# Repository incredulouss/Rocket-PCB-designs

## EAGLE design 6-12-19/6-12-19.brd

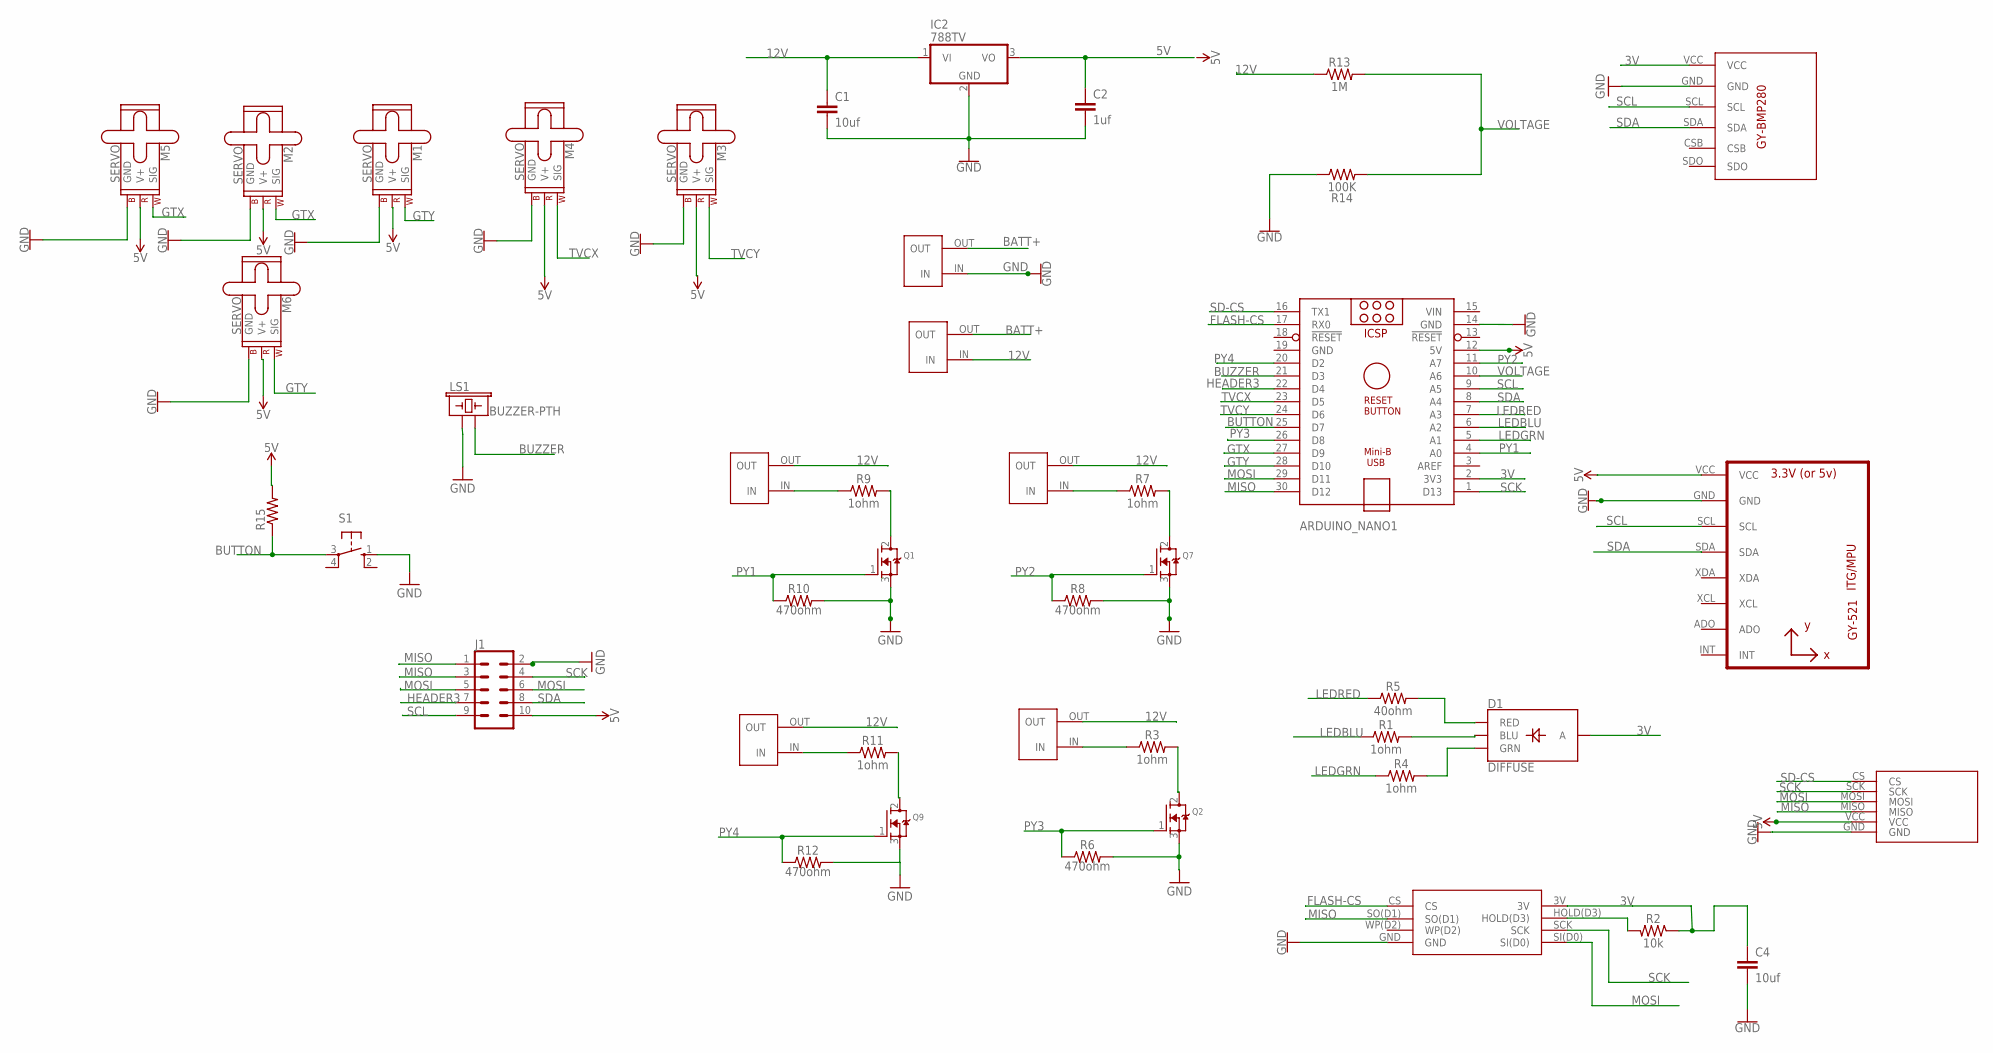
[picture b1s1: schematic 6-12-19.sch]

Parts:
ARDUINO_NANO1: ARDUINO_NANO
C1, C4: 10uf; CAP-PTH-2.54
C2: 1uf; CAP-PTH-2.54
D1: DIFFUSE; LED-RGB-THRU
IC2: 788TV; TO220V
J1: CONN_05X2NO_SILK; 2X5_NOSILK
LS1: BUZZER-PTH; BUZZER-12MM
M1, M2, M3, M4, M5, M6: SERVO; 1X03
Q1, Q2, Q7, Q9: MOSFET-NGDS_TO220V; TO220V
R1, R3, R4, R7, R9, R11: 1ohm; AXIAL-0.3
R2: 10k; AXIAL-0.3
R5: 40ohm; AXIAL-0.3
R6, R8, R10, R12: 470ohm; AXIAL-0.3
R13: 1M; AXIAL-0.3
R14: 100K; AXIAL-0.3
R15: FLIPFLOP-RES; 0805-THM
S1: 40-XX; B3F-40XX
U1: GY-521MPU6050; GY-521
U$1, U$6, U$7, U$11, U$13, U$31: TERMINALBLOCK
U$2: W25Q32FV
U$8: GY-BMP280
U$9: MICROSDCARD

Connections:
3V: ARDUINO_NANO1.2 (3V3), C4.1, D1.2 (A), R2.P$1 (1), U$2.3V, U$8.VCC
5V: ARDUINO_NANO1.12 (5V), C2.1, IC2.3 (VO), J1.10, M1.2 (V+), M2.2 (V+), M3.2 (V+), M4.2 (V+), M5.2 (V+), M6.2 (V+), R15.2, U1.VCC, U$9.VCC
12V: C1.1, IC2.1 (VI), R13.P$1 (1), U$1.IN, U$7.OUT, U$11.OUT, U$13.OUT, U$31.OUT
BATT+: U$1.OUT, U$6.OUT
BUTTON: ARDUINO_NANO1.25 (D7), R15.1, S1.3
BUZZER: ARDUINO_NANO1.21 (D3), LS1.- (2)
FLASH-CS: ARDUINO_NANO1.17 (RX0), U$2.CS
GND: ARDUINO_NANO1.14 (GND), ARDUINO_NANO1.19 (GND), C1.2, C2.2, C4.2, IC2.2 (GND), J1.2, LS1.+ (1), M1.3 (GND), M2.3 (GND), M3.3 (GND), M4.3 (GND), M5.3 (GND), M6.3 (GND), Q1.3 (S), Q2.3 (S), Q7.3 (S), Q9.3 (S), R6.P$2 (2), R8.P$2 (2), R10.P$2 (2), R12.P$2 (2), R14.P$1 (1), S1.1 (S), U1.GND, U$2.GND, U$6.IN, U$8.GND, U$9.GND
GTX: ARDUINO_NANO1.27 (D9), M2.1 (SIG), M5.1 (SIG)
GTY: ARDUINO_NANO1.28 (D10), M1.1 (SIG), M6.1 (SIG)
HEADER3: ARDUINO_NANO1.22 (D4), J1.7
LEDBLU: ARDUINO_NANO1.6 (A2), R1.P$1 (1)
LEDGRN: ARDUINO_NANO1.5 (A1), R4.P$1 (1)
LEDRED: ARDUINO_NANO1.7 (A3), R5.P$1 (1)
MISO: ARDUINO_NANO1.30 (D12), J1.1, J1.3, U$2.SO(D1), U$9.MISO
MOSI: ARDUINO_NANO1.29 (D11), J1.5, J1.6, U$2.SI(D0), U$9.MOSI
unnamed: R2.P$2 (2), U$2.HOLD(D3)
unnamed: R9.P$1 (1), U$31.IN
unnamed: Q1.2 (D), R9.P$2 (2)
unnamed: D1.1 (RED), R5.P$2 (2)
unnamed: D1.4 (BLU), R1.P$2 (2)
unnamed: D1.3 (GRN), R4.P$2 (2)
unnamed: R3.P$1 (1), U$7.IN
unnamed: Q2.2 (D), R3.P$2 (2)
unnamed: Q7.2 (D), R7.P$2 (2)
unnamed: R7.P$1 (1), U$11.IN
unnamed: R11.P$1 (1), U$13.IN
unnamed: Q9.2 (D), R11.P$2 (2)
PY1: ARDUINO_NANO1.4 (A0), Q1.1 (G), R10.P$1 (1)
PY2: ARDUINO_NANO1.11 (A7), Q7.1 (G), R8.P$1 (1)
PY3: ARDUINO_NANO1.26 (D8), Q2.1 (G), R6.P$1 (1)
PY4: ARDUINO_NANO1.20 (D2), Q9.1 (G), R12.P$1 (1)
SCK: ARDUINO_NANO1.1 (D13), J1.4, U$2.SCK, U$9.SCK
SCL: ARDUINO_NANO1.9 (A5), J1.9, U1.SCL, U$8.SCL
SD-CS: ARDUINO_NANO1.16 (TX1), U$9.CS
SDA: ARDUINO_NANO1.8 (A4), J1.8, U1.SDA, U$8.SDA
TVCX: ARDUINO_NANO1.23 (D5), M4.1 (SIG)
TVCY: ARDUINO_NANO1.24 (D6), M3.1 (SIG)
VIN: ARDUINO_NANO1.15 (VIN)
VOLTAGE: ARDUINO_NANO1.10 (A6), R13.P$2 (2), R14.P$2 (2)

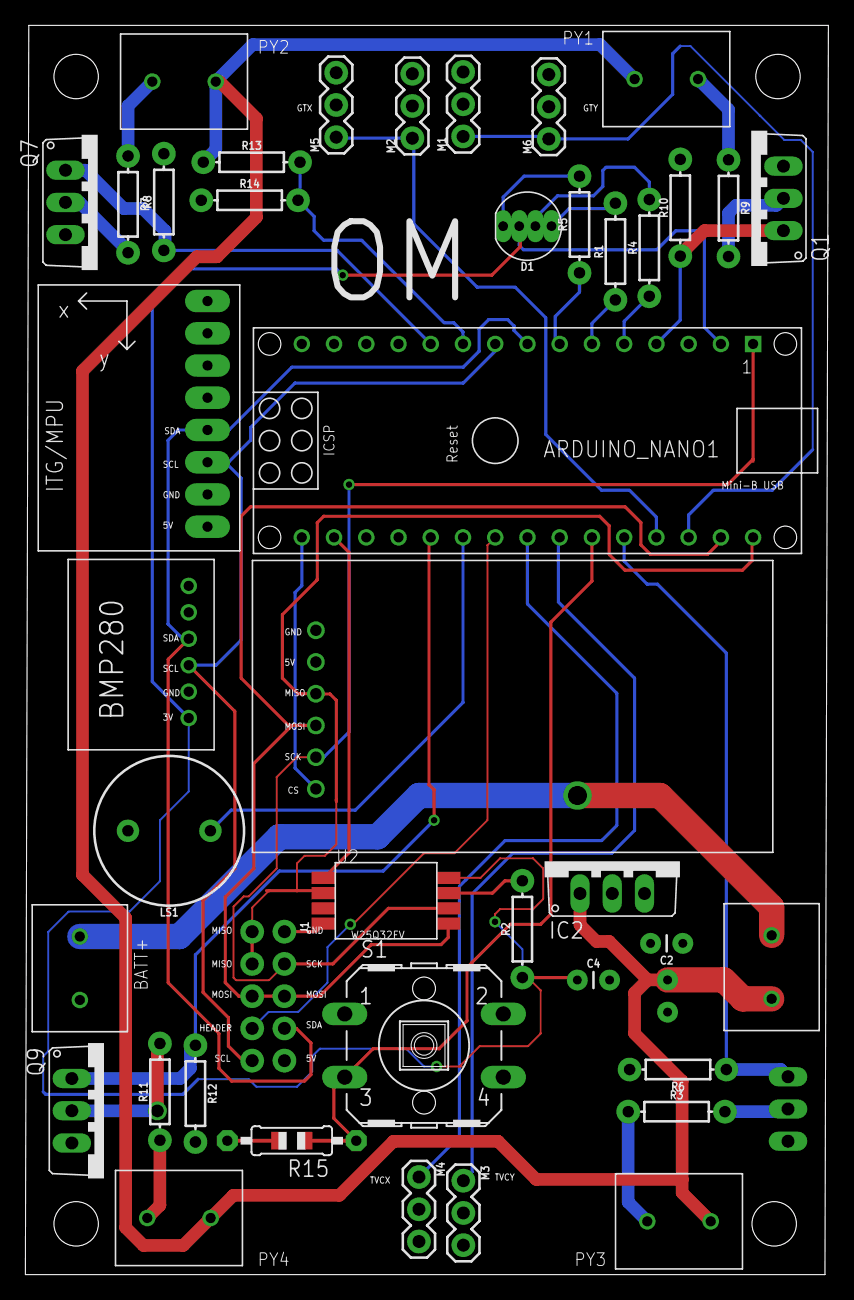
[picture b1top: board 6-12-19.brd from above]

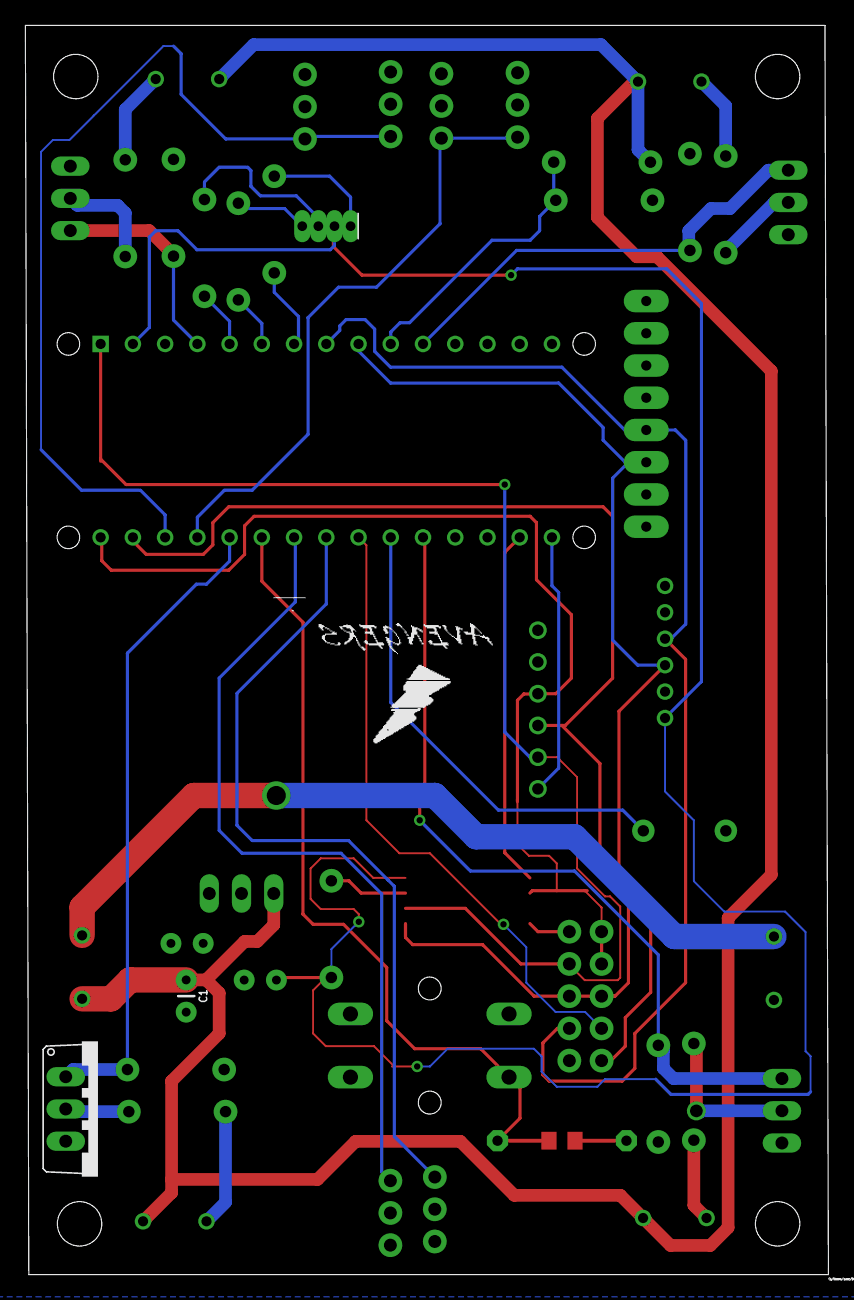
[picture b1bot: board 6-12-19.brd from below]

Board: 2 copper layers, 63.3 x 98.4 mm, 44 parts (2 on the bottom side), 39 nets.

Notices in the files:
parts and their libraries:
SparkFun-Capacitors: Licensing: Creative Commons ShareAlike 4.0 International - https://creativecommons.org/licenses/by-sa/4.0
